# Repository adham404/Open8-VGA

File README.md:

# Open8-VGA

A self-contained 8-bit computer built from 74HC/AC logic chips: a custom microcoded CPU,
32 KiB of RAM, an 80 × 30 VGA text and tile display, a PS/2 keyboard and an EEPROM for
saving programs. It boots straight into a full-screen editor with a built-in assembler, so
you type assembly language on the machine itself and run it, up to games like Tetris and a
scrolling platformer.

**[Try it in your browser →](https://adham404.github.io/Open8-VGA/)** The emulator runs
the real boot ROM, so it is the same machine code the board would run.

Designed by **Adham Elshafei** · adham_mohsen@outlook.com · 2026.
Inspired by Ben Eater's 8-bit breadboard computer.

## Status

Everything is verified in simulation; **no board has been built yet.**

| Area | State | Docs |
|---|---|---|
| Architecture, memory map | done | [01](docs/01-architecture.md) |
| Instruction set (102 instructions), microcode, ROM-based ALU, assembler | done, simulated | [02](docs/02-isa.md) |
| VGA tile controller, PS/2 receiver | done, simulated | [03](docs/03-video-keyboard.md) |
| Boot firmware: editor, on-board assembler, help, examples | done, simulated | [04](docs/04-firmware.md) |
| Tetris, platformer, browser emulator | done, simulated | [05](docs/05-games.md) |
| Save/load to EEPROM (4 slots) | done, simulated | [06](docs/06-eeprom.md) |
| Parts verification and timing budget against datasheets | done | [07](docs/07-parts-timing.md) |
| Netlist, gate-level simulation of the whole board | done, 11 tests | [08](docs/08-board.md) |
| PCB Rev A: 6 layers, routed, design-rule check clean, Gerbers | done, **not fabricated** | [08](docs/08-board.md) |
| Parts list, assembly guide | done | [09](docs/09-assembly.md) |
| Bring-up plan | written, not yet carried out | [10](docs/10-bring-up.md) |
| Compact-Mac-style 3D-printed case with an 8" LCD (FreeCAD) | designed, fit-checked, **not printed** | [enclosure](enclosure/README.md) |

## Quick start

Needs only Python 3.8+ (no packages). Node.js is used by one test.

```sh
./build.sh
```

This builds every ROM image into `build/rom/`, rebuilds the browser emulator
(`web/open8-vga.html`), regenerates the instruction-set doc, and runs the whole test suite.

* Run the emulator locally: open `web/open8-vga.html` in a browser. It is one
  self-contained file and needs no server.
* Assemble a program on your computer: `python3 tools/asm.py prog.asm -o prog.bin --listing prog.lst`
* Run only the tests: `python3 -m unittest discover -s tests`

## Building the hardware

The Rev A board is 313 × 259.5 mm, 6 layers, all through-hole parts (hand assembly), with
the nine flash chips in sockets.

| File | What |
|---|---|
| [`hardware/fab/rev-a/open8-vga-gerbers-revA.zip`](hardware/fab/rev-a/open8-vga-gerbers-revA.zip) | Gerbers and drill files (JLCPCB-ready) |
| [`hardware/fab/rev-a/open8-vga-bom-revA.csv`](hardware/fab/rev-a/open8-vga-bom-revA.csv) | parts list with manufacturer part numbers |
| [`kicad/board/`](kicad/board/) | KiCad 10 project: schematic and routed board |
| [`docs/09-assembly.md`](docs/09-assembly.md) | soldering order, which ROM image goes in which socket, jumpers |
| [`docs/10-bring-up.md`](docs/10-bring-up.md) | staged power-on and test plan |

The ROM images to program into the flash chips come from `./build.sh` (`build/rom/`).
This design has not been built or tested on real hardware; treat Rev A as a first
prototype.

## Repository layout

```
docs/        design notes 01-10, screenshots (02-isa.md is generated)
firmware/    boot firmware in Open8 assembly (main.asm includes the rest; gen/ is generated)
examples/    example programs, all built into the ROM (F5 in the editor)
tools/       ISA definition, ALU and microcode generators, assembler, simulators,
             VGA timing and font generators, firmware and emulator builders
             (web/open8core.js + web/page.html are the emulator sources)
web/         open8-vga.html: the built browser emulator
hardware/    design.py: the board netlist as code; gatesim.py: gate-level simulator;
             lib.py: chip models; kicad_map.py, bom.py; layout/: placement, routing and
             finishing scripts for the PCB; fab/: release fabrication files
kicad/board/ KiCad project for the PCB
enclosure/   3D-printed case: parametric FreeCAD script, STLs, renders
tests/       CPU, assembler, video, keyboard, firmware, games, EEPROM, emulator and
             gate-level board tests
```

## How it is verified

* **CPU:** every opcode, step and flag combination of the microcode is checked against an
  instruction-level reference model; the ALU lookup tables are checked exhaustively.
* **Firmware:** the real flash image boots, edits, assembles and runs programs in the
  simulator; the on-board assembler is byte-identical to the reference assembler.
* **Emulator:** the JavaScript emulator is checked state-for-state against the Python
  simulator.
* **Board:** the full netlist runs at gate level and boots the firmware, draws video and
  reads the keyboard and EEPROM, matching the higher-level simulators.
* **Not yet verified:** a real board, real chip timing (only a datasheet budget so far),
  analog VGA levels, a real keyboard.

## License

[MIT](LICENSE) © 2026 Adham Elshafei. This covers the software, firmware, hardware design
files and documentation.

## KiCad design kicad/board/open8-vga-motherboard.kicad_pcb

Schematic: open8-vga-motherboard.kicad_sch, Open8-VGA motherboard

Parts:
BZ1: piezo; Buzzer_12x9.5RM7.6
C1, C2, C7, C8, C9, C10, C11, C12, C13, C14, C15, C16, C17, C18, C19, C20, C21, C22, C23, C24, C25, C26, C27, C28, C29, C30, C31, C32, C33, C34, C35, C36, C37, C38, C39, C40, C41, C42, C43, C44, C45, C46, C47, C48, C49, C50, C51, C52, C53, C54, C55, C56, C57, C58, C59, C60, C61, C62, C63, C64, C65, C66, C67, C68, C69, C70, C71, C72, C73, C74, C75, C76, C77, C78, C79, C80, C81, C82, C83, C84, C85, C86, C87, C88, C89, C90, C91, C92, C93, C94, C95, C96, C97, C98, C99, C100, C101, C102, C103, C104, C105, C106, C107, C108, C109, C110, C111, C112, C113, C114, C115, C116, C117, C118, C119, C120, C121, C122, C123, C124, C125, C126, C127, C128, C129, C130, C131, C132, C133, C134, C135, C136, C137, C138: 100n; C_Disc_D5.0mm_W2.5mm_P5.00mm
C3: 1u; C_Disc_D5.0mm_W2.5mm_P5.00mm
C4: 10n; C_Disc_D5.0mm_W2.5mm_P5.00mm
C5: 47n; C_Disc_D5.0mm_W2.5mm_P5.00mm
C6: 470u; CP_Radial_D10.0mm_P5.00mm
D1: 1N4148; D_DO-35_SOD27_P7.62mm_Horizontal; MPN 1N4148
D2: SMBJ5.0A; D_SMB; MPN SMBJ5.0A
D3: PWR; LED_D3.0mm
D4: HALT; LED_D3.0mm
F1: 200mA; Fuse_1812_4532Metric; MPN MF-MSMF020-2
F2: 2A; Fuse_1812_4532Metric; MPN MF-MSMF200-2
J1: PS/2; DC-IN-TH_MD-60SM; MPN MD-60SM
J2: VGA; DSUB-15-HD_Socket_Horizontal_P2.29x1.90mm_EdgePinOffset3.03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
J3: USB-C power; USB_C_Receptacle_GCT_USB4125-xx-x_6P_TopMnt_Horizontal
J4: LOGIC; PinHeader_2x20_P2.54mm_Vertical
J5: EXPANSION; PinHeader_2x20_P2.54mm_Vertical
JP1: HALF; PinHeader_1x02_P2.54mm_Vertical
JP2: MCBANK; PinHeader_1x02_P2.54mm_Vertical
JP3: COL_R; PinHeader_1x02_P2.54mm_Vertical
JP4: COL_G; PinHeader_1x02_P2.54mm_Vertical
JP5: COL_B; PinHeader_1x02_P2.54mm_Vertical
Q1: 2N3904; TO-92_Inline; MPN 2N3904
R1, R5, R6, R11, R13, R15: 10k; R_Axial_DIN0207_L6.3mm_D2.5mm_P10.16mm_Horizontal
R2, R3, R10: 47k; R_Axial_DIN0207_L6.3mm_D2.5mm_P10.16mm_Horizontal
R4, R7, R21, R22: 1k; R_Axial_DIN0207_L6.3mm_D2.5mm_P10.16mm_Horizontal
R8, R9: 4.7k; R_Axial_DIN0207_L6.3mm_D2.5mm_P10.16mm_Horizontal
R12, R14, R16: 470; R_Axial_DIN0207_L6.3mm_D2.5mm_P10.16mm_Horizontal
R17, R18: 100; R_Axial_DIN0207_L6.3mm_D2.5mm_P10.16mm_Horizontal
R19, R20: 5.1k; R_Axial_DIN0207_L6.3mm_D2.5mm_P10.16mm_Horizontal
RN1, RN2: 10k; R_Array_SIP9
RV1: 1M; Potentiometer_Bourns_3386P_Vertical
SW1: RESET; SW_PUSH_6mm
SW2: RUN/STEP; SW_Slide_SPDT_Straight_CK_OS102011MS2Q
SW3: STEP/SLOW; SW_Slide_SPDT_Straight_CK_OS102011MS2Q
SW4: STEP; SW_PUSH_6mm
SW5: CONTINUE; SW_PUSH_6mm
U1: 74AC161; DIP-16_W7.62mm; MPN CD74AC161E
U2, U130: 74AC04; DIP-14_W7.62mm; MPN CD74AC04E
U3, U113: 74HC86; DIP-14_W7.62mm; MPN CD74HC86E
U4, U14, U68, U72, U83, U98: 74HC08; DIP-14_W7.62mm; MPN CD74HC08E
U5, U109, U127, U129: 74AC574; DIP-20_W7.62mm; MPN CD74AC574E
U6, U48, U82, U96, U124: 74HC04; DIP-14_W7.62mm; MPN CD74HC04E
U7: MCP130-450; TO-92_Inline; MPN MCP130-450DI/TO
U8, U12, U15, U84, U85, U87: 74HC74; DIP-14_W7.62mm; MPN CD74HC74E
U9, U91: 74HC14; DIP-14_W7.62mm; MPN CD74HC14E
U10: NE555; DIP-8_W7.62mm; MPN NE555P
U11, U70, U71, U74: 74HC157; DIP-16_W7.62mm; MPN CD74HC157E
U13, U25, U26, U27, U69, U86, U99: 74HC32; DIP-14_W7.62mm; MPN CD74HC32E
U16, U131: 74AC08; DIP-14_W7.62mm; MPN CD74AC08E
U17, U18, U19, U108, U200: SST39SF010A; DIP-32_W15.24mm_Socket; MPN SST39SF010A-70-4C-PHE
U20, U100: 74HC02; DIP-14_W7.62mm; MPN CD74HC02E
U21, U49, U50, U51, U52, U103, U104, U105, U106, U107: 74HC163; DIP-16_W7.62mm; MPN CD74HC163E
U22, U30, U32, U34, U36, U37, U55, U56, U57, U78, U79, U80, U81: 74HC377; DIP-20_W7.62mm; MPN CD74HC377E
U23, U24: 74HC154; DIP-24_W15.24mm; MPN CD74HC154E
U28, U29, U59, U60, U61, U62, U63, U64, U65, U66: 74HC153; DIP-16_W7.62mm; MPN CD74HC153E
U31, U33, U35, U46, U47, U53, U54, U58, U88, U89, U101, U102: 74HC541; DIP-20_W7.62mm; MPN CD74HC541E
U38, U39, U40, U41: SST39SF040; DIP-32_W15.24mm_Socket; MPN SST39SF040-70-4C-PHE
U42, U43, U44, U45, U94: 74HC161; DIP-16_W7.62mm; MPN CD74HC161E
U67: 74AC138; DIP-16_W7.62mm; MPN CD74AC138E
U73, U117: 74HC00; DIP-14_W7.62mm; MPN CD74HC00E
U75, U76, U77: 74HC138; DIP-16_W7.62mm; MPN CD74HC138E
U90: 25LC512; DIP-8_W7.62mm; MPN 25LC512-I/P
U92, U93: 74HC164; DIP-14_W7.62mm; MPN CD74HC164E
U95, U123: 74HC11; DIP-14_W7.62mm; MPN CD74HC11E
U97: 74HC05; DIP-14_W7.62mm; MPN SN74HC05N
U110, U111, U112: 74HC283; DIP-16_W7.62mm; MPN CD74HC283E
U114, U115, U116, U120, U121, U122: 74AC157; DIP-16_W7.62mm; MPN CD74AC157E
U118, U125: 74AC245; DIP-20_W7.62mm; MPN CD74AC245E
U119, U126: 74HC574; DIP-20_W7.62mm; MPN CD74HC574E
U128: 74AC151; DIP-16_W7.62mm; MPN CD74AC151E
U201: AS6C62256; DIP-28_W15.24mm; MPN AS6C62256-55PCN
U202, U203: AS6C6264; DIP-28_W15.24mm; MPN AS6C6264-55PCN
X1: 25.175MHz; Oscillator_DIP-14; MPN ECS-100A-251.7

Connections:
A0: J4.1, J5.9, U49.3 (D0), U59.7 (Za), U75.1 (A0), U76.1 (A0), U77.1 (A0), U114.3 (I1a), U120.3 (I1a), U200.12 (A0), U201.10 (A0)
A1: J4.2, J5.10, U49.4 (D1), U59.9 (Zb), U75.2 (A1), U76.2 (A1), U77.2 (A1), U114.6 (I1b), U120.6 (I1b), U200.11 (A1), U201.9 (A1)
A2: J4.3, J5.11, U49.5 (D2), U60.7 (Za), U75.3 (A2), U76.3 (A2), U77.3 (A2), U114.10 (I1c), U120.10 (I1c), U200.10 (A2), U201.8 (A2)
A3: J4.4, J5.12, U49.6 (D3), U60.9 (Zb), U114.13 (I1d), U120.13 (I1d), U200.9 (A3), U201.7 (A3)
A4: J4.5, J5.13, U50.3 (D0), U61.7 (Za), U115.3 (I1a), U121.3 (I1a), U200.8 (A4), U201.6 (A4)
A5: J4.6, J5.14, U50.4 (D1), U61.9 (Zb), U115.6 (I1b), U121.6 (I1b), U200.7 (A5), U201.5 (A5)
A6: J4.7, J5.15, U50.5 (D2), U62.7 (Za), U115.10 (I1c), U121.10 (I1c), U200.6 (A6), U201.4 (A6)
A7: J4.8, J5.16, U50.6 (D3), U62.9 (Zb), U115.13 (I1d), U121.13 (I1d), U200.5 (A7), U201.3 (A7)
A8: J4.9, U51.3 (D0), U63.7 (Za), U116.3 (I1a), U122.3 (I1a), U200.27 (A8), U201.25 (A8)
A9: J4.10, U51.4 (D1), U63.9 (Zb), U116.6 (I1b), U122.6 (I1b), U200.26 (A9), U201.24 (A9)
A10: J4.11, U51.5 (D2), U64.7 (Za), U116.10 (I1c), U122.10 (I1c), U200.23 (A10), U201.21 (A10)
A11: J4.12, U51.6 (D3), U64.9 (Zb), U116.13 (I1d), U122.13 (I1d), U200.25 (A11), U201.23 (A11)
A12: J4.13, U52.3 (D0), U65.7 (Za), U67.1 (A0), U68.13, U70.2 (I0a), U201.2 (A12)
A13: J4.14, U52.4 (D1), U65.9 (Zb), U67.2 (A1), U68.12, U70.5 (I0b), U201.26 (A13)
A14: J4.15, U52.5 (D2), U66.7 (Za), U67.3 (A2), U69.4, U70.1 (S), U71.1 (S), U201.1 (A14)
A14OR: U69.6, U72.2
A15: J4.16, U48.3, U52.6 (D3), U66.9 (Zb), U67.4 (~E0), U72.1, U74.3 (I1a)
A15_N: U48.4, U201.20 (~CS)
A1312: U68.11, U69.5
AF0_0: U28.6 (I0a), U40.13 (D0)
AF0_1: U28.10 (I0b), U40.14 (D1)
AF0_2: U29.6 (I0a), U40.15 (D2)
AF0_3: U29.10 (I0b), U40.17 (D3)
AF1_0: U28.5 (I1a), U41.13 (D0)
AF1_1: U28.11 (I1b), U41.14 (D1)
AF1_2: U29.5 (I1a), U41.15 (D2)
AF1_3: U29.11 (I1b), U41.17 (D3)
ALUOP3_N: U6.12, U27.13
AQ0: U32.2 (Q0), U33.2 (A0)
AQ1: U32.5 (Q1), U33.3 (A1)
AQ2: U32.6 (Q2), U33.4 (A2)
AQ3: U32.9 (Q3), U33.5 (A3)
AQ4: U32.12 (Q4), U33.6 (A4)
AQ5: U32.15 (Q5), U33.7 (A5)
AQ6: U32.16 (Q6), U33.8 (A6)
AQ7: U32.19 (Q7), U33.9 (A7)
BANKW_N: U77.12 (~Y3), U78.1 (~E)
BK0: U70.3 (I1a), U78.2 (Q0)
BK1: U70.6 (I1b), U78.5 (Q1)
BK2: U70.10 (I1c), U78.6 (Q2)
BK3: U70.13 (I1d), U78.9 (Q3)
BK4: U71.3 (I1a), U78.12 (Q4)
BLANK: U109.17 (Q2), U129.3 (D1)
BLANKQ: U129.18 (Q1), U130.1
BLOCK: U48.9, U72.6, U83.2
BLOCK_N: U48.8, U72.10
BQ0: U34.2 (Q0), U35.2 (A0)
BQ1: U34.5 (Q1), U35.3 (A1)
BQ2: U34.6 (Q2), U35.4 (A2)
BQ3: U34.9 (Q3), U35.5 (A3)
BQ4: U34.12 (Q4), U35.6 (A4)
BQ5: U34.15 (Q5), U35.7 (A5)
BQ6: U34.16 (Q6), U35.8 (A6)
BQ7: U34.19 (Q7), U35.9 (A7)
CC1: U110.9 (C4), U111.7 (C0)
CE_ANY: U13.6, U13.9
CE_L: U15.5 (Q), U16.2
CE_RAW: U13.8, U15.2 (D)
CE_RUN: U4.11, U13.4
CE_STEP: U13.5, U14.3
CH0: U119.19 (Q0), U121.2 (I0a)
CH1: U119.18 (Q1), U121.5 (I0b)
CH2: U119.17 (Q2), U121.11 (I0c)
CH3: U119.16 (Q3), U121.14 (I0d)
CH4: U119.15 (Q4), U122.2 (I0a)
CH5: U119.14 (Q5), U122.5 (I0b)
CH6: U119.13 (Q6), U122.11 (I0c)
CH7: U119.12 (Q7), U122.14 (I0d)
CHARCLK: J4.38, U2.2, U8.3 (C), U8.11 (C), U12.3 (C), U12.11 (C), U16.1, U87.3 (C), U103.2 (CP), U104.2 (CP), U105.2 (CP), U106.2 (CP), U107.2 (CP), U109.11 (Cp), U127.11 (Cp)
COL0: U110.4 (S1), U114.2 (I0a)
COL1: U110.1 (S2), U114.5 (I0b)
COL2: U110.13 (S3), U114.11 (I0c)
COL3: U110.10 (S4), U114.14 (I0d)
COL4: U111.4 (S1), U115.2 (I0a)
COL5: U111.1 (S2), U115.5 (I0b)
COL6: U111.13 (S3), U115.11 (I0c)
COLEN_B: JP5.1, R15.1, U131.13
COLEN_G: JP4.1, R13.1, U131.10
COLEN_R: JP3.1, R11.1, U131.5
CONT: U9.4, U9.5
CONTBTN_RC: C2.1, R3.1, SW5.1, U9.3
CONT_N: U9.6, U14.4
CPUCLK: J4.25, J5.20, U15.11 (C), U16.3, U21.2 (CP), U22.11 (CP), U30.11 (CP), U32.11 (CP), U34.11 (CP), U36.11 (CP), U37.11 (CP), U42.2 (CP), U43.2 (CP), U44.2 (CP), U45.2 (CP), U49.2 (CP), U50.2 (CP), U51.2 (CP), U52.2 (CP), U55.11 (CP), U56.11 (CP), U57.11 (CP), U78.11 (CP), U79.11 (CP), U80.11 (CP), U81.11 (CP), U84.3 (C), U84.11 (C), U85.3 (C), U85.11 (C), U87.11 (C)
CTRL555: C4.1, U10.5 (CONT)
D0: J4.17, J5.1, RN1.2 (R1), U22.3 (D0), U28.3 (I3a), U28.4 (I2a), U31.18 (Y0), U32.3 (D0), U33.18 (Y0), U34.3 (D0), U35.18 (Y0), U36.3 (D0), U37.3 (D0), U38.13 (D0), U39.13 (D0), U42.3 (D0), U44.3 (D0), U46.18 (Y0), U47.18 (Y0), U53.18 (Y0), U54.18 (Y0), U55.3 (D0), U56.3 (D0), U57.3 (D0), U58.18 (Y0), U78.3 (D0), U79.3 (D0), U80.3 (D0), U81.3 (D0), U88.18 (Y0), U89.18 (Y0), U101.18 (Y0), U102.18 (Y0), U118.2 (A0), U125.2 (A0), U200.13 (D0), U201.11 (Q0)
D1: J4.18, J5.2, RN1.3 (R2), U22.4 (D1), U28.12 (I2b), U28.13 (I3b), U31.17 (Y1), U32.4 (D1), U33.17 (Y1), U34.4 (D1), U35.17 (Y1), U36.4 (D1), U37.4 (D1), U38.14 (D1), U39.14 (D1), U42.4 (D1), U44.4 (D1), U46.17 (Y1), U47.17 (Y1), U53.17 (Y1), U54.17 (Y1), U55.4 (D1), U56.4 (D1), U57.4 (D1), U58.17 (Y1), U78.4 (D1), U79.4 (D1), U80.4 (D1), U81.4 (D1), U88.17 (Y1), U89.17 (Y1), U101.17 (Y1), U102.17 (Y1), U118.3 (A1), U125.3 (A1), U200.14 (D1), U201.12 (Q1)
D2: J4.19, J5.3, RN1.4 (R3), U22.7 (D2), U29.3 (I3a), U29.4 (I2a), U31.16 (Y2), U32.7 (D2), U33.16 (Y2), U34.7 (D2), U35.16 (Y2), U36.7 (D2), U37.7 (D2), U38.15 (D2), U39.15 (D2), U42.5 (D2), U44.5 (D2), U46.16 (Y2), U47.16 (Y2), U53.16 (Y2), U54.16 (Y2), U55.7 (D2), U56.7 (D2), U57.7 (D2), U58.16 (Y2), U78.7 (D2), U79.7 (D2), U80.7 (D2), U81.7 (D2), U88.16 (Y2), U89.16 (Y2), U101.16 (Y2), U102.16 (Y2), U118.4 (A2), U125.4 (A2), U200.15 (D2), U201.13 (Q2)
D3: J4.20, J5.4, RN1.5 (R4), U22.8 (D3), U29.12 (I2b), U29.13 (I3b), U31.15 (Y3), U32.8 (D3), U33.15 (Y3), U34.8 (D3), U35.15 (Y3), U36.8 (D3), U37.8 (D3), U38.17 (D3), U39.17 (D3), U42.6 (D3), U44.6 (D3), U46.15 (Y3), U47.15 (Y3), U53.15 (Y3), U54.15 (Y3), U55.8 (D3), U56.8 (D3), U57.8 (D3), U58.15 (Y3), U78.8 (D3), U79.8 (D3), U80.8 (D3), U81.8 (D3), U88.15 (Y3), U89.15 (Y3), U101.15 (Y3), U102.15 (Y3), U118.5 (A3), U125.5 (A3), U200.17 (D3), U201.15 (Q3)
D4: J4.21, J5.5, RN1.6 (R5), U22.13 (D4), U31.14 (Y4), U32.13 (D4), U33.14 (Y4), U34.13 (D4), U35.14 (Y4), U36.13 (D4), U37.13 (D4), U38.18 (D4), U39.18 (D4), U43.3 (D0), U45.3 (D0), U46.14 (Y4), U47.14 (Y4), U53.14 (Y4), U54.14 (Y4), U55.13 (D4), U56.13 (D4), U57.13 (D4), U58.14 (Y4), U78.13 (D4), U79.13 (D4), U80.13 (D4), U81.13 (D4), U88.14 (Y4), U89.14 (Y4), U101.14 (Y4), U102.14 (Y4), U118.6 (A4), U125.6 (A4), U200.18 (D4), U201.16 (Q4)
D5: J4.22, J5.6, RN1.7 (R6), U22.14 (D5), U31.13 (Y5), U32.14 (D5), U33.13 (Y5), U34.14 (D5), U35.13 (Y5), U36.14 (D5), U37.14 (D5), U38.19 (D5), U39.19 (D5), U43.4 (D1), U45.4 (D1), U46.13 (Y5), U47.13 (Y5), U53.13 (Y5), U54.13 (Y5), U55.14 (D5), U56.14 (D5), U57.14 (D5), U58.13 (Y5), U78.14 (D5), U79.14 (D5), U80.14 (D5), U81.14 (D5), U88.13 (Y5), U89.13 (Y5), U101.13 (Y5), U102.13 (Y5), U118.7 (A5), U125.7 (A5), U200.19 (D5), U201.17 (Q5)
D6: J4.23, J5.7, RN1.8 (R7), U22.17 (D6), U31.12 (Y6), U32.17 (D6), U33.12 (Y6), U34.17 (D6), U35.12 (Y6), U36.17 (D6), U37.17 (D6), U38.20 (D6), U39.20 (D6), U43.5 (D2), U45.5 (D2), U46.12 (Y6), U47.12 (Y6), U53.12 (Y6), U54.12 (Y6), U55.17 (D6), U56.17 (D6), U57.17 (D6), U58.12 (Y6), U78.17 (D6), U79.17 (D6), U80.17 (D6), U81.17 (D6), U88.12 (Y6), U89.12 (Y6), U101.12 (Y6), U102.12 (Y6), U118.8 (A6), U125.8 (A6), U200.20 (D6), U201.18 (Q6)
D7: J4.24, J5.8, RN1.9 (R8), U22.18 (D7), U31.11 (Y7), U32.18 (D7), U33.11 (Y7), U34.18 (D7), U35.11 (Y7), U36.18 (D7), U37.18 (D7), U38.21 (D7), U39.21 (D7), U43.6 (D3), U45.6 (D3), U46.11 (Y7), U47.11 (Y7), U53.11 (Y7), U54.11 (Y7), U55.18 (D7), U56.18 (D7), U57.18 (D7), U58.11 (Y7), U78.18 (D7), U79.18 (D7), U80.18 (D7), U81.18 (D7), U88.11 (Y7), U89.11 (Y7), U101.11 (Y7), U102.11 (Y7), U118.9 (A7), U125.9 (A7), U200.21 (D7), U201.19 (Q7)
D555: R4.2, RV1.1, U10.7 (DISCH)
DOT0: U1.14 (Q0), U3.1, U128.11 (S0)
DOT1: U1.13 (Q1), U3.2, U128.10 (S1)
DOT2: U1.12 (Q2), U2.1, U4.1, U5.3 (D1), U15.3 (C), U119.11 (Cp), U126.11 (Cp), U128.9 (S2)
DOTCLK: U1.2 (CP), U2.3, U129.11 (Cp), X1.8 (OUT)
DOTCLK_N: U2.4, U5.11 (Cp)
DOTX: U3.3, U4.2
EE_CS_N: U86.6, U90.1 (~CS)
EE_MOSI: U81.5 (Q1), U90.5 (MOSI)
EE_SCK: U81.2 (Q0), U90.6 (SCK)
EXIN1: J5.26, RN2.3 (R2), U89.3 (A1)
EXIN2: J5.27, RN2.4 (R3), U89.4 (A2)
EXIN3: J5.28, RN2.5 (R4), U89.5 (A3)
EXIN4: J5.29, RN2.6 (R5), U89.6 (A4)
EXIN5: J5.30, RN2.7 (R6), U89.7 (A5)
EXIN6: J5.31, RN2.8 (R7), U89.8 (A6)
EXIN7: J5.32, RN2.9 (R8), U89.9 (A7)
FAD0: U120.4 (Za), U203.10 (A0)
FAD1: U120.7 (Zb), U203.9 (A1)
FAD2: U120.9 (Zc), U203.8 (A2)
FAD3: U120.12 (Zd), U203.7 (A3)
FAD4: U121.4 (Za), U203.6 (A4)
FAD5: U121.7 (Zb), U203.5 (A5)
FAD6: U121.9 (Zc), U203.4 (A6)
FAD7: U121.12 (Zd), U203.3 (A7)
FAD8: U122.4 (Za), U203.25 (A8)
FAD9: U122.7 (Zb), U203.24 (A9)
FAD10: U122.9 (Zc), U203.21 (A10)
FAD11: U122.12 (Zd), U203.23 (A11)
FBEN: U123.6, U124.1
FBOE_N: U124.2, U125.19 (CE)
FD0: U125.18 (B0), U126.2 (D0), U203.11 (I/O0)
FD1: U125.17 (B1), U126.3 (D1), U203.12 (I/O1)
FD2: U125.16 (B2), U126.4 (D2), U203.13 (I/O2)
FD3: U125.15 (B3), U126.5 (D3), U203.15 (I/O3)
FD4: U125.14 (B4), U126.6 (D4), U203.16 (I/O4)
FD5: U125.13 (B5), U126.7 (D5), U203.17 (I/O5)
FD6: U125.12 (B6), U126.8 (D6), U203.18 (I/O6)
FD7: U125.11 (B7), U126.9 (D7), U203.19 (I/O7)
FL0: U126.19 (Q0), U127.2 (D0)
FL1: U126.18 (Q1), U127.3 (D1)
FL2: U126.17 (Q2), U127.4 (D2)
FL3: U126.16 (Q3), U127.5 (D3)
FL4: U126.15 (Q4), U127.6 (D4)
FL5: U126.14 (Q5), U127.7 (D5)
FL6: U126.13 (Q6), U127.8 (D6)
FL7: U126.12 (Q7), U127.9 (D7)
FLAGLD_N: U20.4, U30.1 (~E)
FLAGSBUS: U6.10, U20.6, U28.2 (S1), U29.2 (S1)
FLAG_C: U17.12 (A0), U18.12 (A0), U19.12 (A0), U30.2 (Q0), U31.2 (A0)
FLAG_N: U17.10 (A2), U18.10 (A2), U19.10 (A2), U30.6 (Q2), U31.4 (A2)
FLAG_V: U17.9 (A3), U18.9 (A3), U19.9 (A3), U30.9 (Q3), U31.5 (A3)
FLAG_Z: U17.11 (A1), U18.11 (A1), U19.11 (A1), U30.5 (Q1), U31.3 (A1)
FN0: U28.7 (Za), U30.3 (D0)
FN1: U28.9 (Zb), U30.4 (D1)
FN2: U29.7 (Za), U30.7 (D2)
FN3: U29.9 (Zb), U30.8 (D3)
FNOE_N: U123.12, U203.22 (~OE)
FNSEL: U96.10, U117.10, U123.2, U123.4
FNSEL_N: U67.7 (~Y7), U96.11
FNWE_N: U117.8, U203.27 (~WE)
FROMRAM: U72.5, U74.2 (I0a), U87.9 (Q)
FR_D: U74.4 (Za), U87.12 (D)
GND: C1.2, C2.2, C3.2, C4.2, C5.2, C6.2, C7.2, C8.2, C9.2, C10.2, C11.2, C12.2, C13.2, C14.2, C15.2, C16.2, C17.2, C18.2, C19.2, C20.2, C21.2, C22.2, C23.2, C24.2, C25.2, C26.2, C27.2, C28.2, C29.2, C30.2, C31.2, C32.2, C33.2, C34.2, C35.2, C36.2, C37.2, C38.2, C39.2, C40.2, C41.2, C42.2, C43.2, C44.2, C45.2, C46.2, C47.2, C48.2, C49.2, C50.2, C51.2, C52.2, C53.2, C54.2, C55.2, C56.2, C57.2, C58.2, C59.2, C60.2, C61.2, C62.2, C63.2, C64.2, C65.2, C66.2, C67.2, C68.2, C69.2, C70.2, C71.2, C72.2, C73.2, C74.2, C75.2, C76.2, C77.2, C78.2, C79.2, C80.2, C81.2, C82.2, C83.2, C84.2, C85.2, C86.2, C87.2, C88.2, C89.2, C90.2, C91.2, C92.2, C93.2, C94.2, C95.2, C96.2, C97.2, C98.2, C99.2, C100.2, C101.2, C102.2, C103.2, C104.2, C105.2, C106.2, C107.2, C108.2, C109.2, C110.2, C111.2, C112.2, C113.2, C114.2, C115.2, C116.2, C117.2, C118.2, C119.2, C120.2, C121.2, C122.2, C123.2, C124.2, C125.2, C126.2, C127.2, C128.2, C129.2, C130.2, C131.2, C132.2, C133.2, C134.2, C135.2, C136.2, C137.2, C138.2, D2.2 (A2), D3.1 (K), D4.1 (K), J1.3, J1.7, J1.8, J1.9, J2.5, J2.6, J2.7, J2.8, J2.10, J2.SH, J3.A12 (GND), J3.B12 (GND), J3.SH (SHIELD), J4.40, J5.35, J5.36, J5.37, Q1.1 (E), R5.2, R6.2, R11.2, R13.2, R15.2, R19.2, R20.2, SW1.2, SW2.3 (C), SW3.3 (C), SW4.2, SW5.2, U1.3 (D0), U1.4 (D1), U1.5 (D2), U1.6 (D3), U1.8 (GND), U2.5, U2.7 (GND), U2.9, U2.11, U2.13, U3.4, U3.5, U3.7 (GND), U3.9, U3.10, U3.12, U3.13, U4.7 (GND), U5.1 (OE), U5.4 (D2), U5.5 (D3), U5.6 (D4), U5.7 (D5), U5.8 (D6), U5.9 (D7), U5.10 (GND), U6.7 (GND), U7.3 (VSS), U8.7 (GND), U9.7 (GND), U9.9, U9.11, U9.13, U10.1 (GND), U11.5 (I0b), U11.6 (I1b), U11.8 (GND), U11.10 (I1c), U11.11 (I0c), U11.13 (I1d), U11.14 (I0d), U11.15 (E), U12.7 (GND), U13.7 (GND), U14.7 (GND), U15.7 (GND), U16.4, U16.5, U16.7 (GND), U16.9, U16.10, U16.12, U16.13, U17.1 (A18), U17.16 (GND), U17.22 (CE), U17.24 (OE), U17.30 (A17), U18.1 (A18), U18.16 (GND), U18.22 (CE), U18.24 (OE), U18.30 (A17), U19.1 (A18), U19.16 (GND), U19.22 (CE), U19.24 (OE), U19.30 (A17), U20.7 (GND), U20.11, U20.12, U21.3 (D0), U21.4 (D1), U21.5 (D2), U21.6 (D3), U21.8 (GND), U22.10 (GND), U23.12 (GND), U23.18 (E0), U23.19 (E1), U24.12 (GND), U24.18 (E0), U24.19 (E1), U25.7 (GND), U26.7 (GND), U27.7 (GND), U28.1 (Ea), U28.8 (GND), U28.15 (Eb), U29.1 (Ea), U29.8 (GND), U29.15 (Eb), U30.10 (GND), U30.13 (D4), U30.14 (D5), U30.17 (D6), U30.18 (D7), U31.6 (A4), U31.7 (A5), U31.8 (A6), U31.9 (A7), U31.10 (GND), U31.19 (G2), U32.10 (GND), U33.10 (GND), U33.19 (G2), U34.10 (GND), U35.10 (GND), U35.19 (G2), U36.10 (GND), U37.10 (GND), U38.16 (GND), U38.22 (CE), U39.16 (GND), U39.22 (CE), U40.16 (GND), U40.22 (CE), U40.24 (OE), U41.16 (GND), U41.22 (CE), U41.24 (OE), U42.8 (GND), U43.8 (GND), U44.8 (GND), U45.8 (GND), U46.10 (GND), U46.19 (G2), U47.10 (GND), U47.19 (G2), U48.7 (GND), U49.8 (GND), U50.8 (GND), U51.8 (GND), U52.8 (GND), U53.10 (GND), U53.19 (G2), U54.10 (GND), U54.19 (G2), U55.10 (GND), U56.10 (GND), U57.10 (GND), U58.10 (GND), U58.19 (G2), U59.1 (Ea), U59.8 (GND)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
H0: U103.14 (Q0), U108.12 (A0), U110.5 (A1)
H1: U103.13 (Q1), U108.11 (A1), U110.3 (A2)
H2: U103.12 (Q2), U108.10 (A2), U110.14 (A3)
H3: U103.11 (Q3), U108.9 (A3), U110.12 (A4)
H4: U104.14 (Q0), U108.8 (A4), U111.5 (A1)
H5: U104.13 (Q1), U108.7 (A5), U111.3 (A2)
H6: U104.12 (Q2), U108.6 (A6), U111.14 (A3)
HALFOK: U4.13, U13.3
HALF_EN: JP1.1, R5.1, U6.9
HALF_N: U6.8, U13.2
HALTED: R22.1, U13.13, U15.9 (Q)
HALTED_N: U4.10, U15.8 (~Q)
HALT_D: U13.11, U15.12 (D)
HALT_LED: D4.2 (A), R22.2
HC0: U103.15 (TC), U104.10 (CET)
HCLR_N: U14.6, U15.13 (~R)
HRESET: U96.3, U105.7 (CEP), U105.10 (CET), U106.7 (CEP), U107.7 (CEP), U109.16 (Q3)
HRES_N: U96.4, U103.1 (~MR), U104.1 (~MR)
HSQ: J4.34, R17.1, U129.17 (Q2)
HSYNC_N: U109.19 (Q0), U129.4 (D2)
IN_RD_N: U75.7 (~Y7), U89.1 (G1)
IOSEL_N: J5.17, U67.10 (~Y5), U75.4 (~E0), U76.4 (~E0), U77.4 (~E0)
IR0: U17.27 (A8), U18.27 (A8), U19.27 (A8), U22.2 (Q0)
IR1: U17.26 (A9), U18.26 (A9), U19.26 (A9), U22.5 (Q1)
IR2: U17.23 (A10), U18.23 (A10), U19.23 (A10), U22.6 (Q2)
IR3: U17.25 (A11), U18.25 (A11), U19.25 (A11), U22.9 (Q3)
IR4: U17.4 (A12), U18.4 (A12), U19.4 (A12), U22.12 (Q4)
IR5: U17.28 (A13), U18.28 (A13), U19.28 (A13), U22.15 (Q5)
IR6: U17.29 (A14), U18.29 (A14), U19.29 (A14), U22.16 (Q6)
IR7: U17.3 (A15), U18.3 (A15), U19.3 (A15), U22.19 (Q7)
KBD_RAW: U48.12, U84.2 (D)
KBD_RAW_N: U48.13, U76.15 (~Y0)
KBD_RD_N: U75.15 (~Y0), U101.1 (G1)
KCLK: D1.1 (K), J1.5, J4.36, R8.1, U91.1, U97.2
KCLKI_N: U91.2, U92.8 (CP), U93.8 (CP), U94.2 (CP)
KCLR: U84.5 (Q), U99.1
KCLR_ANY: U99.3, U100.2
KCLR_N: U94.1 (~MR), U100.1
KDATA: J1.1, J4.37, R9.1, U91.3
KDATA_N: U91.4, U91.5
KDATI: U91.6, U92.1 (DSA)
KP0: U92.3 (Q0), U102.5 (A3)
KP1: U92.4 (Q1), U102.3 (A1)
KP2: U92.5 (Q2), U101.9 (A7)
KP3: U92.6 (Q3), U101.8 (A6)
KP4: U92.10 (Q4), U101.7 (A5)
KP5: U92.11 (Q5), U101.6 (A4)
KP6: U92.12 (Q6), U101.5 (A3)
KP7: U92.13 (Q7), U93.1 (DSA), U101.4 (A2)
KP8: U93.3 (Q0), U101.3 (A1)
KP9: U93.4 (Q1), U101.2 (A0)
KP10: U93.5 (Q2), U102.4 (A2)
KQ0: U94.14 (Q0), U95.1
KQ1: U94.13 (Q1), U95.2
KQ3: U94.11 (Q3), U95.13
KREADY: U95.12, U96.1, U97.1, U102.2 (A0)
KREADY_N: U94.7 (CEP), U94.10 (CET), U96.2, U98.2
KST_RD_N: U75.14 (~Y1), U102.1 (G1)
KTO: U91.10, U98.1
KTO_CLR: U98.3, U99.2
KTO_N: U91.8, U91.11
KTO_RC: C5.1, D1.2 (A), R10.2, U91.9
KVCC: F1.2, J1.4
LD_A_N: U24.2 (S1), U32.1 (~E)
LD_B_N: U24.3 (S2), U34.1 (~E)
LD_FLAGSBUS_N: U6.11, U24.14 (S12)
LD_IR: U48.10, U74.1 (S)
LD_IR_N: U22.1 (~E), U24.6 (S5), U48.11
LD_L_N: U24.5 (S4), U36.1 (~E)
LD_MARH_N: U24.8 (S7), U56.1 (~E)
LD_MARL_N: U24.7 (S6), U55.1 (~E)
LD_SP_N: U24.11 (S10), U57.1 (~E)
LD_T_N: U24.4 (S3), U37.1 (~E)
LD_XH_N: U24.10 (S9), U44.9 (~PE), U45.9 (~PE)
LD_XL_N: U24.9 (S8), U42.9 (~PE), U43.9 (~PE)
LQ0: U36.2 (Q0), U38.25 (A11), U39.25 (A11), U40.25 (A11), U41.25 (A11)
LQ1: U36.5 (Q1), U38.4 (A12), U39.4 (A12), U40.4 (A12), U41.4 (A12)
LQ2: U36.6 (Q2), U38.28 (A13), U39.28 (A13), U40.28 (A13), U41.28 (A13)
LQ3: U36.9 (Q3), U38.29 (A14), U39.29 (A14), U40.29 (A14), U41.29 (A14)
LQ4: U36.12 (Q4), U38.3 (A15), U39.3 (A15), U40.3 (A15), U41.3 (A15)
LQ5: U36.15 (Q5), U38.2 (A16), U39.2 (A16), U40.2 (A16), U41.2 (A16)
LQ6: U36.16 (Q6), U38.30 (A17), U39.30 (A17), U40.30 (A17), U41.30 (A17)
LQ7: U36.19 (Q7), U38.1 (A18), U39.1 (A18), U40.1 (A18), U41.1 (A18)
M0: U55.2 (Q0), U59.5 (I1a)
M1: U55.5 (Q1), U59.11 (I1b)
M2: U55.6 (Q2), U60.5 (I1a)
M3: U55.9 (Q3), U60.11 (I1b)
M4: U55.12 (Q4), U61.5 (I1a)
M5: U55.15 (Q5), U61.11 (I1b)
M6: U55.16 (Q6), U62.5 (I1a)
M7: U55.19 (Q7), U62.11 (I1b)
M8: U56.2 (Q0), U63.5 (I1a)
M9: U56.5 (Q1), U63.11 (I1b)
M10: U56.6 (Q2), U64.5 (I1a)
M11: U56.9 (Q3), U64.11 (I1b)
M12: U56.12 (Q4), U65.5 (I1a)
M13: U56.15 (Q5), U65.11 (I1b)
M14: U56.16 (Q6), U66.5 (I1a)
M15: U56.19 (Q7), U66.11 (I1b)
MC0: U17.13 (D0), U23.23 (A0)
MC1: U17.14 (D1), U23.22 (A1)
MC2: U17.15 (D2), U23.21 (A2)
MC3: U17.17 (D3), U23.20 (A3)
MC4: U17.18 (D4), U24.23 (A0)
MC5: U17.19 (D5), U24.22 (A1)
MC6: U17.20 (D6), U24.21 (A2)
MC7: U17.21 (D7), U24.20 (A3)
MC8: U18.13 (D0), U38.12 (A0), U39.12 (A0), U40.12 (A0), U41.12 (A0)
MC9: U18.14 (D1), U38.11 (A1), U39.11 (A1), U40.11 (A1), U41.11 (A1)
MC10: U18.15 (D2), U38.10 (A2), U39.10 (A2), U40.10 (A2), U41.10 (A2)
MC11: U6.13, U18.17 (D3), U27.10, U28.14 (S0), U29.14 (S0)
MC12: U18.18 (D4), U59.14 (S0), U60.14 (S0), U61.14 (S0), U62.14 (S0), U63.14 (S0), U64.14 (S0), U65.14 (S0), U66.14 (S0)
MC13: U18.19 (D5), U59.2 (S1), U60.2 (S1), U61.2 (S1), U62.2 (S1), U63.2 (S1), U64.2 (S1), U65.2 (S1), U66.2 (S1)
MC14: U18.20 (D6), U49.7 (CEP), U49.10 (CET), U50.7 (CEP), U51.7 (CEP), U52.7 (CEP)
MC15: U18.21 (D7), U48.1
MC16: U19.13 (D0), U42.7 (CEP), U42.10 (CET), U43.7 (CEP), U44.7 (CEP), U45.7 (CEP)
MC17: U19.14 (D1), U20.5
MC18: U19.15 (D2), U20.2
MC19: U13.12, U19.17 (D3)
MC20: U19.18 (D4), U20.8
MC21: U19.19 (D5), U69.9
MC22: U19.20 (D6)
MC23: U19.21 (D7)
MCBANK: JP2.1, R6.1, U17.2 (A16), U18.2 (A16), U19.2 (A16)
MEMOP: U95.11, U117.3, U123.5
MISO: RN2.2 (R1), U89.2 (A0), U90.2 (MISO)
OE_ALU_N: U25.8, U27.9, U27.12
OE_AR0_N: U27.8, U38.24 (OE)
OE_AR1_N: U27.11, U39.24 (OE)
OE_A_N: U25.3, U33.1 (G1)
OE_B_N: U25.6, U35.1 (G1)
OE_FLAGS_N: U27.3, U31.1 (G1)
OE_PCH_N: U26.11, U54.1 (G1)
OE_PCL_N: U26.8, U53.1 (G1)
OE_SP_N: U26.6, U58.1 (G1)
OE_XH_N: U26.3, U47.1 (G1)
OE_XL_N: U25.11, U46.1 (G1)
OUT2: U81.6 (Q2), U86.4
OUT3: R7.1, U81.9 (Q3)
OUT4: J5.22, U81.12 (Q4)
OUT5: J5.23, U81.15 (Q5)
OUT6: J5.24, U81.16 (Q6)
OUT7: J5.25, U81.19 (Q7)
OUTW_N: U77.9 (~Y6), U81.1 (~E)
P0: U49.14 (Q0), U53.2 (A0), U59.6 (I0a)
P1: U49.13 (Q1), U53.3 (A1), U59.10 (I0b)
P2: U49.12 (Q2), U53.4 (A2), U60.6 (I0a)
P3: U49.11 (Q3), U53.5 (A3), U60.10 (I0b)
P4: U50.14 (Q0), U53.6 (A4), U61.6 (I0a)
P5: U50.13 (Q1), U53.7 (A5), U61.10 (I0b)
P6: U50.12 (Q2), U53.8 (A6), U62.6 (I0a)
P7: U50.11 (Q3), U53.9 (A7), U62.10 (I0b)
P8: U51.14 (Q0), U54.2 (A0), U63.6 (I0a)
P9: U51.13 (Q1), U54.3 (A1), U63.10 (I0b)
P10: U51.12 (Q2), U54.4 (A2), U64.6 (I0a)
P11: U51.11 (Q3), U54.5 (A3), U64.10 (I0b)
P12: U52.14 (Q0), U54.6 (A4), U65.6 (I0a)
P13: U52.13 (Q1), U54.7 (A5), U65.10 (I0b)
P14: U52.12 (Q2), U54.8 (A6), U66.6 (I0a)
P15: U52.11 (Q3), U54.9 (A7), U66.10 (I0b)
PC0: U49.15 (TC), U50.10 (CET)
PC1: U50.15 (TC), U51.10 (CET)
PC2: U51.15 (TC), U52.10 (CET)
PCCLR_N: U20.10, U49.1 (~MR), U50.1 (~MR), U51.1 (~MR), U52.1 (~MR)
PCLOAD_N: U48.2, U49.9 (~PE), U50.9 (~PE), U51.9 (~PE), U52.9 (~PE)
PH2: U5.18 (Q1), U95.3, U114.1 (S), U115.1 (S), U116.1 (S), U120.1 (S), U121.1 (S), U122.1 (S), U123.1
PIXQ: U129.19 (Q0), U131.1
PIXR: U128.5 (Z), U129.2 (D0)
PROT: U72.3, U72.4
PULSE: U4.6, U14.2
PWR_LED: D3.2 (A), R21.2
PX0: U127.19 (Q0), U128.12 (I7)
PX1: U127.18 (Q1), U128.13 (I6)
PX2: U127.17 (Q2), U128.14 (I5)
PX3: U127.16 (Q3), U128.15 (I4)
PX4: U127.15 (Q4), U128.1 (I3)
PX5: U127.14 (Q5), U128.2 (I2)
PX6: U127.13 (Q6), U128.3 (I1)
PX7: U127.12 (Q7), U128.4 (I0)
RA12: U70.4 (Za), U200.4 (A12)
RA13: U70.7 (Zb), U200.28 (A13)
RA14: U70.9 (Zc), U200.29 (A14)
RA15: U70.12 (Zd), U200.3 (A15)
RA16: U71.4 (Za), U200.2 (A16)
RAMWE_N: U73.3, U201.27 (~WE)
RC1: U112.9 (C4), U113.5
RD_N: J4.32, J5.18, U27.6, U69.2, U75.5 (~E1), U201.22 (~OE)
RG0_N: U14.9, U67.15 (~Y0)
RG01_N: U14.8, U68.1
RG1_N: U14.10, U67.14 (~Y1)
RG2_N: U14.12, U67.13 (~Y2)
RG3_N: U14.13, U67.12 (~Y3)
RG03_N: U68.3, U68.4
RG4_N: U67.11 (~Y4), U68.5
RG23_N: U14.11, U68.2
ROMOE_N: U69.3, U200.24 (OE)
ROMSEL_N: J4.33, U68.6, U69.1
ROW0: U112.4 (S1), U115.14 (I0d)
ROW1: U112.1 (S2), U116.2 (I0a)
ROW2: U112.13 (S3), U116.5 (I0b)
ROW3: U112.10 (S4), U116.11 (I0c)
ROW4: U113.6, U116.14 (I0d)
ROWX: U113.3, U113.4
RST: U6.4, U13.10, U20.3, U20.9, U86.5, U100.3
RSTRAW_N: R1.1, SW1.1, U7.1 (~RST), U8.2 (D)
RST_N: J4.26, J5.21, U6.3, U8.5 (Q), U14.5, U84.1 (~R), U84.13 (~R), U85.1 (~R), U85.13 (~R)
RUN: U4.9, U6.6
RUNOK: U4.8, U4.12
S0: U57.2 (Q0), U58.2 (A0), U59.3 (I3a)
S1: U57.5 (Q1), U58.3 (A1), U59.13 (I3b)
S2: U57.6 (Q2), U58.4 (A2), U60.3 (I3a)
S3: U57.9 (Q3), U58.5 (A3), U60.13 (I3b)
S4: U57.12 (Q4), U58.6 (A4), U61.3 (I3a)
S5: U57.15 (Q5), U58.7 (A5), U61.13 (I3b)
S6: U57.16 (Q6), U58.8 (A6), U62.3 (I3a)
S7: U57.19 (Q7), U58.9 (A7), U62.13 (I3b)
SLOWCLK: U10.3 (OUT), U11.3 (I1a)
SLOW_SEL: SW3.2 (B), U11.1 (S)
SPK_B: Q1.2 (B), R7.2
SPK_C: BZ1.2 (-), Q1.3 (C)
SRC_ALU_N: U23.4 (S3), U25.9
SRC_A_N: U23.2 (S1), U25.1
SRC_B_N: U23.3 (S2), U25.4
SRC_FLAGS_N: U23.11 (S10), U27.1
SRC_MEM_N: U23.5 (S4), U27.4, U76.5 (~E1), U117.1
SRC_PCH_N: U23.10 (S9), U26.12
SRC_PCL_N: U23.9 (S8), U26.9
SRC_SP_N: U23.8 (S7), U26.4
SRC_XH_N: U23.7 (S6), U26.1
SRC_XL_N: U23.6 (S5), U25.12
STEP0: J4.27, U17.8 (A4), U18.8 (A4), U19.8 (A4), U21.14 (Q0)
STEP1: J4.28, U17.7 (A5), U18.7 (A5), U19.7 (A5), U21.13 (Q1)
STEP2: J4.29, U17.6 (A6), U18.6 (A6), U19.6 (A6), U21.12 (Q2)
STEP3: J4.30, U17.5 (A7), U18.5 (A7), U19.5 (A7), U21.11 (Q3)
STEPBTN: U9.2, U11.2 (I0a)
STEPBTN_RC: C1.1, R2.1, SW4.1, U9.1
STEPCLR_N: U20.1, U21.1 (~MR)
STEPSRC: U11.4 (Za), U12.2 (D)
STEPSYNC1: U4.4, U12.5 (Q), U12.12 (D)
STEPSYNC2_N: U4.5, U12.8 (~Q)
STEP_MODE: SW2.2 (B), U6.5, U14.1
SX0: U79.2 (Q0), U110.6 (B1)
SX1: U79.5 (Q1), U110.2 (B2)
SX2: U79.6 (Q2), U110.15 (B3)
SX3: U79.9 (Q3), U110.11 (B4)
SX4: U79.12 (Q4), U111.6 (B1)
SX5: U79.15 (Q5), U111.2 (B2)
SX6: U79.16 (Q6), U111.15 (B3)
SXW_N: U77.11 (~Y4), U79.1 (~E)
SY0: U80.2 (Q0), U112.6 (B1)
SY1: U80.5 (Q1), U112.2 (B2)
SY2: U80.6 (Q2), U112.15 (B3)
SY3: U80.9 (Q3), U112.11 (B4)
SY4: U80.12 (Q4), U113.2
SYSW_N: U72.13, U77.13 (~Y2), U83.5
SYS_RAW: U82.2, U84.12 (D)
SYS_RAW_N: U76.13 (~Y2), U82.1
SYS_RD_N: U75.13 (~Y2), U88.1 (G1)
SYW_N: U77.10 (~Y5), U80.1 (~E)
T555: C3.1, RV1.2, RV1.3, U10.2 (TRIG), U10.6 (THRES)
TOG: U8.9 (Q), U13.1
TOG_N: U8.8 (~Q), U8.12 (D)
TQ0: U37.2 (Q0), U38.9 (A3), U39.9 (A3), U40.9 (A3), U41.9 (A3)
TQ1: U37.5 (Q1), U38.8 (A4), U39.8 (A4), U40.8 (A4), U41.8 (A4)
TQ2: U37.6 (Q2), U38.7 (A5), U39.7 (A5), U40.7 (A5), U41.7 (A5)
TQ3: U37.9 (Q3), U38.6 (A6), U39.6 (A6), U40.6 (A6), U41.6 (A6)
TQ4: U37.12 (Q4), U38.5 (A7), U39.5 (A7), U40.5 (A7), U41.5 (A7)
TQ5: U37.15 (Q5), U38.27 (A8), U39.27 (A8), U40.27 (A8), U41.27 (A8)
TQ6: U37.16 (Q6), U38.26 (A9), U39.26 (A9), U40.26 (A9), U41.26 (A9)
TQ7: U37.19 (Q7), U38.23 (A10), U39.23 (A10), U40.23 (A10), U41.23 (A10)
TR0: U108.13 (D0), U109.2 (D0)
TR1: U108.14 (D1), U109.3 (D1)
TR2: U108.15 (D2), U109.4 (D2)
TR3: U108.17 (D3), U109.5 (D3)
TR4: U108.18 (D4), U109.6 (D4)
TR5: U108.19 (D5), U109.7 (D5)
TRAPF: U72.12, U85.5 (Q), U88.3 (A1)
TRAP_D: U69.8, U85.2 (D)
TRAP_K: U69.10, U72.11
UNBLANK: U130.2, U131.2
USB_CC1: J3.A5 (CC1), R19.1
USB_CC2: J3.B5 (CC2), R20.1
V0: U105.14 (Q0), U108.5 (A7), U120.2 (I0a)
V1: U105.13 (Q1), U108.27 (A8), U120.5 (I0b)
V2: U105.12 (Q2), U108.26 (A9), U120.11 (I0c)
V3: U105.11 (Q3), U108.23 (A10), U120.14 (I0d)
V4: U106.14 (Q0), U108.25 (A11), U112.5 (A1)
V5: U106.13 (Q1), U108.4 (A12), U112.3 (A2)
V6: U106.12 (Q2), U108.28 (A13), U112.14 (A3)
V7: U106.11 (Q3), U108.29 (A14), U112.12 (A4)
V8: U107.14 (Q0), U108.3 (A15), U113.1
V9: U107.13 (Q1), U108.2 (A16)
VAD0: U114.4 (Za), U202.10 (A0)
VAD1: U114.7 (Zb), U202.9 (A1)
VAD2: U114.9 (Zc), U202.8 (A2)
VAD3: U114.12 (Zd), U202.7 (A3)
VAD4: U115.4 (Za), U202.6 (A4)
VAD5: U115.7 (Zb), U202.5 (A5)
VAD6: U115.9 (Zc), U202.4 (A6)
VAD7: U115.12 (Zd), U202.3 (A7)
VAD8: U116.4 (Za), U202.25 (A8)
VAD9: U116.7 (Zb), U202.24 (A9)
VAD10: U116.9 (Zc), U202.21 (A10)
VAD11: U116.12 (Zd), U202.23 (A11)
VB: R16.1, U131.11
VBEN: U95.8, U96.13
VBL: U83.9, U87.5 (Q), U88.2 (A0)
VBLS: U86.1, U109.14 (Q5)
VBL_D: U86.3, U87.2 (D)
VBL_K: U83.8, U86.2
VBOE_N: U96.12, U118.19 (CE)
VBUS: F2.1, J3.A9 (VBUS), J3.B9 (VBUS)
VC0: U105.15 (TC), U106.10 (CET)
VC1: U106.15 (TC), U107.10 (CET)
VCC: BZ1.1 (+), C6.1, C7.1, C8.1, C9.1, C10.1, C11.1, C12.1, C13.1, C14.1, C15.1, C16.1, C17.1, C18.1, C19.1, C20.1, C21.1, C22.1, C23.1, C24.1, C25.1, C26.1, C27.1, C28.1, C29.1, C30.1, C31.1, C32.1, C33.1, C34.1, C35.1, C36.1, C37.1, C38.1, C39.1, C40.1, C41.1, C42.1, C43.1, C44.1, C45.1, C46.1, C47.1, C48.1, C49.1, C50.1, C51.1, C52.1, C53.1, C54.1, C55.1, C56.1, C57.1, C58.1, C59.1, C60.1, C61.1, C62.1, C63.1, C64.1, C65.1, C66.1, C67.1, C68.1, C69.1, C70.1, C71.1, C72.1, C73.1, C74.1, C75.1, C76.1, C77.1, C78.1, C79.1, C80.1, C81.1, C82.1, C83.1, C84.1, C85.1, C86.1, C87.1, C88.1, C89.1, C90.1, C91.1, C92.1, C93.1, C94.1, C95.1, C96.1, C97.1, C98.1, C99.1, C100.1, C101.1, C102.1, C103.1, C104.1, C105.1, C106.1, C107.1, C108.1, C109.1, C110.1, C111.1, C112.1, C113.1, C114.1, C115.1, C116.1, C117.1, C118.1, C119.1, C120.1, C121.1, C122.1, C123.1, C124.1, C125.1, C126.1, C127.1, C128.1, C129.1, C130.1, C131.1, C132.1, C133.1, C134.1, C135.1, C136.1, C137.1, C138.1, D2.1 (A1), F1.1, F2.2, J4.39, J5.33, J5.34, JP1.2, JP2.2, JP3.2, JP4.2, JP5.2, R1.2, R2.2, R3.2, R4.1, R8.2, R9.2, R10.1, R21.1, RN1.1 (common), RN2.1 (common), SW2.1 (A), SW3.1 (A), U1.1 (~MR), U1.7 (CEP), U1.9 (~PE), U1.10 (CET), U1.16 (VCC), U2.14 (VCC), U3.14 (VCC), U4.14 (VCC), U5.20 (VCC), U6.14 (VCC), U7.2 (VDD), U8.1 (~R), U8.4 (~S), U8.10 (~S), U8.13 (~R), U8.14 (VCC), U9.14 (VCC), U10.4 (~RST), U10.8 (VCC), U11.16 (VCC), U12.1 (~R), U12.4 (~S), U12.10 (~S), U12.13 (~R), U12.14 (VCC), U13.14 (VCC), U14.14 (VCC), U15.1 (~R), U15.4 (~S), U15.10 (~S), U15.14 (VCC), U16.14 (VCC), U17.31 (PGM), U17.32 (VCC), U18.31 (PGM), U18.32 (VCC), U19.31 (PGM), U19.32 (VCC), U20.14 (VCC), U21.7 (CEP), U21.9 (~PE), U21.10 (CET), U21.16 (VCC), U22.20 (VCC), U23.24 (VCC), U24.24 (VCC), U25.14 (VCC), U26.14 (VCC), U27.14 (VCC), U28.16 (VCC), U29.16 (VCC), U30.20 (VCC), U31.20 (VCC), U32.20 (VCC), U33.20 (VCC), U34.20 (VCC), U35.20 (VCC), U36.20 (VCC), U37.20 (VCC), U38.31 (PGM), U38.32 (VCC), U39.31 (PGM), U39.32 (VCC), U40.31 (PGM), U40.32 (VCC), U41.31 (PGM), U41.32 (VCC), U42.1 (~MR), U42.16 (VCC), U43.1 (~MR), U43.16 (VCC), U44.1 (~MR), U44.16 (VCC), U45.1 (~MR), U45.16 (VCC), U46.20 (VCC), U47.20 (VCC), U48.14 (VCC), U49.16 (VCC), U50.16 (VCC), U51.16 (VCC), U52.16 (VCC), U53.20 (VCC), U54.20 (VCC), U55.20 (VCC), U56.20 (VCC), U57.20 (VCC), U58.20 (VCC), U59.16 (VCC), U60.16 (VCC), U61.16 (VCC), U62.16 (VCC), U63.3 (I3a), U63.13 (I3b), U63.16 (VCC), U64.3 (I3a), U64.13 (I3b), U64.16 (VCC), U65.13 (I3b), U65.16 (VCC), U66.13 (I3b), U66.16 (VCC), U67.6 (E2), U67.16 (VCC), U68.14 (VCC), U69.14 (VCC), U70.16 (VCC), U71.16 (VCC), U72.14 (VCC), U73.14 (VCC), U74.16 (VCC), U75.6 (E2), U75.16 (VCC), U76.6 (E2), U76.16 (VCC), U77.6 (E2), U77.16 (VCC), U78.20 (VCC), U79.20 (VCC), U80.20 (VCC), U81.20 (VCC), U82.14 (VCC), U83.14 (VCC), U84.4 (~S), U84.10 (~S), U84.14 (VCC), U85.4 (~S), U85.10 (~S), U85.14 (VCC), U86.14 (VCC), U87.1 (~R), U87.4 (~S), U87.10 (~S), U87.13 (~R), U87.14 (VCC), U88.20 (VCC), U89.20 (VCC), U90.3 (~WP), U90.7 (~HOLD), U90.8 (VCC), U91.14 (VCC), U92.2 (DSB), U92.9 (~MR), U92.14 (VCC), U93.2 (DSB), U93.9 (~MR), U93.14 (VCC), U94.9 (~PE), U94.16 (VCC), U95.14 (VCC), U96.14 (VCC), U97.14 (VCC), U98.14 (VCC), U99.14 (VCC), U100.14 (VCC), U101.20 (VCC), U102.20 (VCC), U103.7 (CEP), U103.9 (~PE)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
VCLR_N: U83.10, U84.8 (~Q)
VD0: U118.18 (B0), U119.2 (D0), U202.11 (I/O0)
VD1: U118.17 (B1), U119.3 (D1), U202.12 (I/O1)
VD2: U118.16 (B2), U119.4 (D2), U202.13 (I/O2)
VD3: U118.15 (B3), U119.5 (D3), U202.15 (I/O3)
VD4: U118.14 (B4), U119.6 (D4), U202.16 (I/O4)
VD5: U118.13 (B5), U119.7 (D5), U202.17 (I/O5)
VD6: U118.12 (B6), U119.8 (D6), U202.18 (I/O6)
VD7: U118.11 (B7), U119.9 (D7), U202.19 (I/O7)
VG: R14.1, U131.8
VGA_B: J2.3, R16.2
VGA_G: J2.2, R14.2
VGA_HS: J2.13, R17.2
VGA_R: J2.1, R12.2
VGA_VS: J2.14, R18.2
VIDEO: U131.3, U131.4, U131.9, U131.12
VIOLEV: U69.12, U83.3
VIOLF: U83.4, U85.9 (Q), U88.4 (A2)
VIOL_D: U69.11, U85.12 (D)
VIOL_K: U69.13, U83.6
VR: R12.1, U131.6
VRESET: U96.5, U109.15 (Q4)
VRES_N: U96.6, U105.1 (~MR), U106.1 (~MR), U107.1 (~MR)
VROE_N: U95.6, U202.22 (~OE)
VRSEL: U95.4, U95.10, U96.8, U117.5
VRSEL_N: U67.9 (~Y6), U96.9
VRWE_N: U117.6, U202.27 (~WE)
VSQ: J4.35, R18.1, U129.16 (Q3)
VSYNC_N: U109.18 (Q1), U129.5 (D3)
WIN: U5.19 (Q0), U6.1, U68.10, U95.9, U123.3
WINRAW: U4.3, U5.2 (D0)
WIN_N: U6.2, U25.2, U25.5, U25.10, U25.13, U26.2, U26.5, U26.10, U26.13, U27.2, U27.5
WR: U48.6, U68.9, U83.1, U95.5, U118.1 (A->B), U123.13, U125.1 (A->B)
WRP: U68.8, U72.9, U117.4, U117.9
WRP_OK: U72.8, U73.1, U73.2
WR_N: J4.31, J5.19, U24.13 (S11), U48.5, U77.5 (~E1), U117.2
X0: U42.14 (Q0), U46.2 (A0), U59.4 (I2a)
X1: U42.13 (Q1), U46.3 (A1), U59.12 (I2b)
X2: U42.12 (Q2), U46.4 (A2), U60.4 (I2a)
X3: U42.11 (Q3), U46.5 (A3), U60.12 (I2b)
X4: U43.14 (Q0), U46.6 (A4), U61.4 (I2a)
X5: U43.13 (Q1), U46.7 (A5), U61.12 (I2b)
X6: U43.12 (Q2), U46.8 (A6), U62.4 (I2a)
X7: U43.11 (Q3), U46.9 (A7), U62.12 (I2b)
X8: U44.14 (Q0), U47.2 (A0), U63.4 (I2a)
X9: U44.13 (Q1), U47.3 (A1), U63.12 (I2b)
X10: U44.12 (Q2), U47.4 (A2), U64.4 (I2a)
X11: U44.11 (Q3), U47.5 (A3), U64.12 (I2b)
X12: U45.14 (Q0), U47.6 (A4), U65.4 (I2a)
X13: U45.13 (Q1), U47.7 (A5), U65.12 (I2b)
X14: U45.12 (Q2), U47.8 (A6), U66.4 (I2a)
X15: U45.11 (Q3), U47.9 (A7), U66.12 (I2b)
XC0: U42.15 (TC), U43.10 (CET)
XC1: U43.15 (TC), U44.10 (CET)
XC2: U44.15 (TC), U45.10 (CET)

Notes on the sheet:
U92 74HC164
U107 74HC163
U117 74HC00
U98 74HC08
Connector — J3 USB-C power
U96 74HC04
U21 74HC163
U62 74HC153
U121 74AC157
U89 74HC541
U61 74HC153
U23 74HC154
Memory — U19 SST39SF010A
U84 74HC74
Memory — U201 AS6C62256
U48 74HC04
Memory — U202 AS6C6264
U72 74HC08
Memory — U203 AS6C6264
J1 PS/2
U88 74HC541
U74 74HC157
U15 74HC74
U8 74HC74
U105 74HC163
U63 74HC153
Memory — U41 SST39SF040
U114 74AC157
U31 74HC541
U102 74HC541
U25 74HC32
U53 74HC541
U103 74HC163
U128 74AC151
U58 74HC541
U124 74HC04
Memory — U200 SST39SF010A
U59 74HC153
U56 74HC377
U73 74HC00

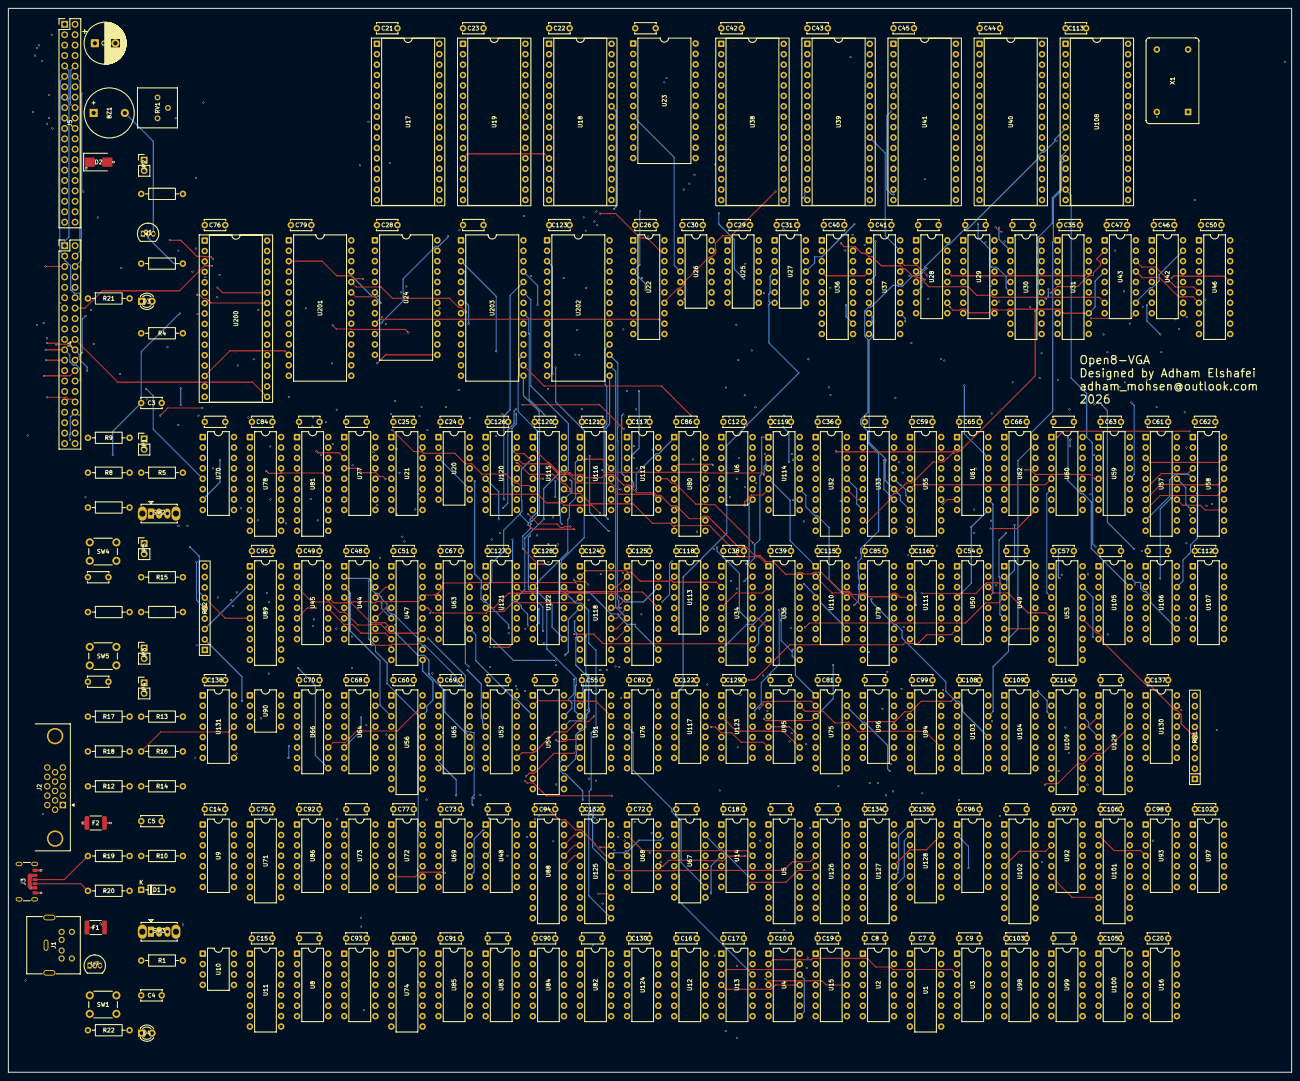
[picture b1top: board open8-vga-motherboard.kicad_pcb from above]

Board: 6 copper layers, 313.0 x 259.5 mm, 322 parts (0 on the bottom side), 524 nets.

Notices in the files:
kicad/board/open8-vga-motherboard.kicad_pcb:
©2026 Adham Elshafei — Rev A
